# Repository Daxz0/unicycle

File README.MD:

# About

i was particulary inspired by instagram reels that showed robots demonstrating PID

i have some new members for my VEX Robotics team who are going to be learning about PID soon for their robots, so I wanted a nice way to demonstrate the concept since there are a lot of other variables when tuning a VEX robot.

### Assembly
The following includes which each component in the BOM.csv correlates to the reference on the PCB:

| Reference        | Component                  |
| ---------------- | -------------------------- |
| C1               | Aluminum Capacitor (100µF) |
| C2               | Aluminum Capacitor (330µF) |
| C3, C5           | Ceramic Capacitor (22µF)   |
| C4, C6, C8, C10  | Ceramic Capacitor (0.1µF)  |
| C7               | Ceramic Capacitor (10nF)   |
| C9               | Ceramic Capacitor (2.2nF)  |
| R1               | Resistor (330Ω)            |
| R4, R7           | Resistor (4.7kΩ)           |
| R5, R6           | Resistor (5.1kΩ)           |
| L1               | Power Inductor             |
| D1, D4           | Schottky Diode             |
| D2               | General Purpose Diode      |
| D3               | LED                        |
| D5               | Schottky Diode (Silicon)   |
| U1               | ESP32-S3-MINI-1-N8         |
| U2               | Buck Regulator             |
| U3               | LDO Regulator              |
| U4               | MPU-6050 (IMU)             |
| F1               | Fuse                       |
| SW1              | Switch                     |
| J1               | Battery Connector (XT30)   |
| J3               | USB-C                      |
| A1               | Motor Driver               |

### Resources
thanks to all these incredible resources that allowed me to put the cad together
- https://grabcad.com/library/nema-17-bracket-1
- https://grabcad.com/library/2s-7-4v-li-po-battery-1
- https://grabcad.com/library/pololu-scooter-skate-wheel-70x25mm-1
- https://a.pololu-files.com/picture/0J5557.600.jpg?7958d675b1fec8d1f6bb65c62e140bbe

note: the adapter for the wheel shaft i made myself as i could not find an existing CAD for it, linked instead is a reference sheet i used to make my own

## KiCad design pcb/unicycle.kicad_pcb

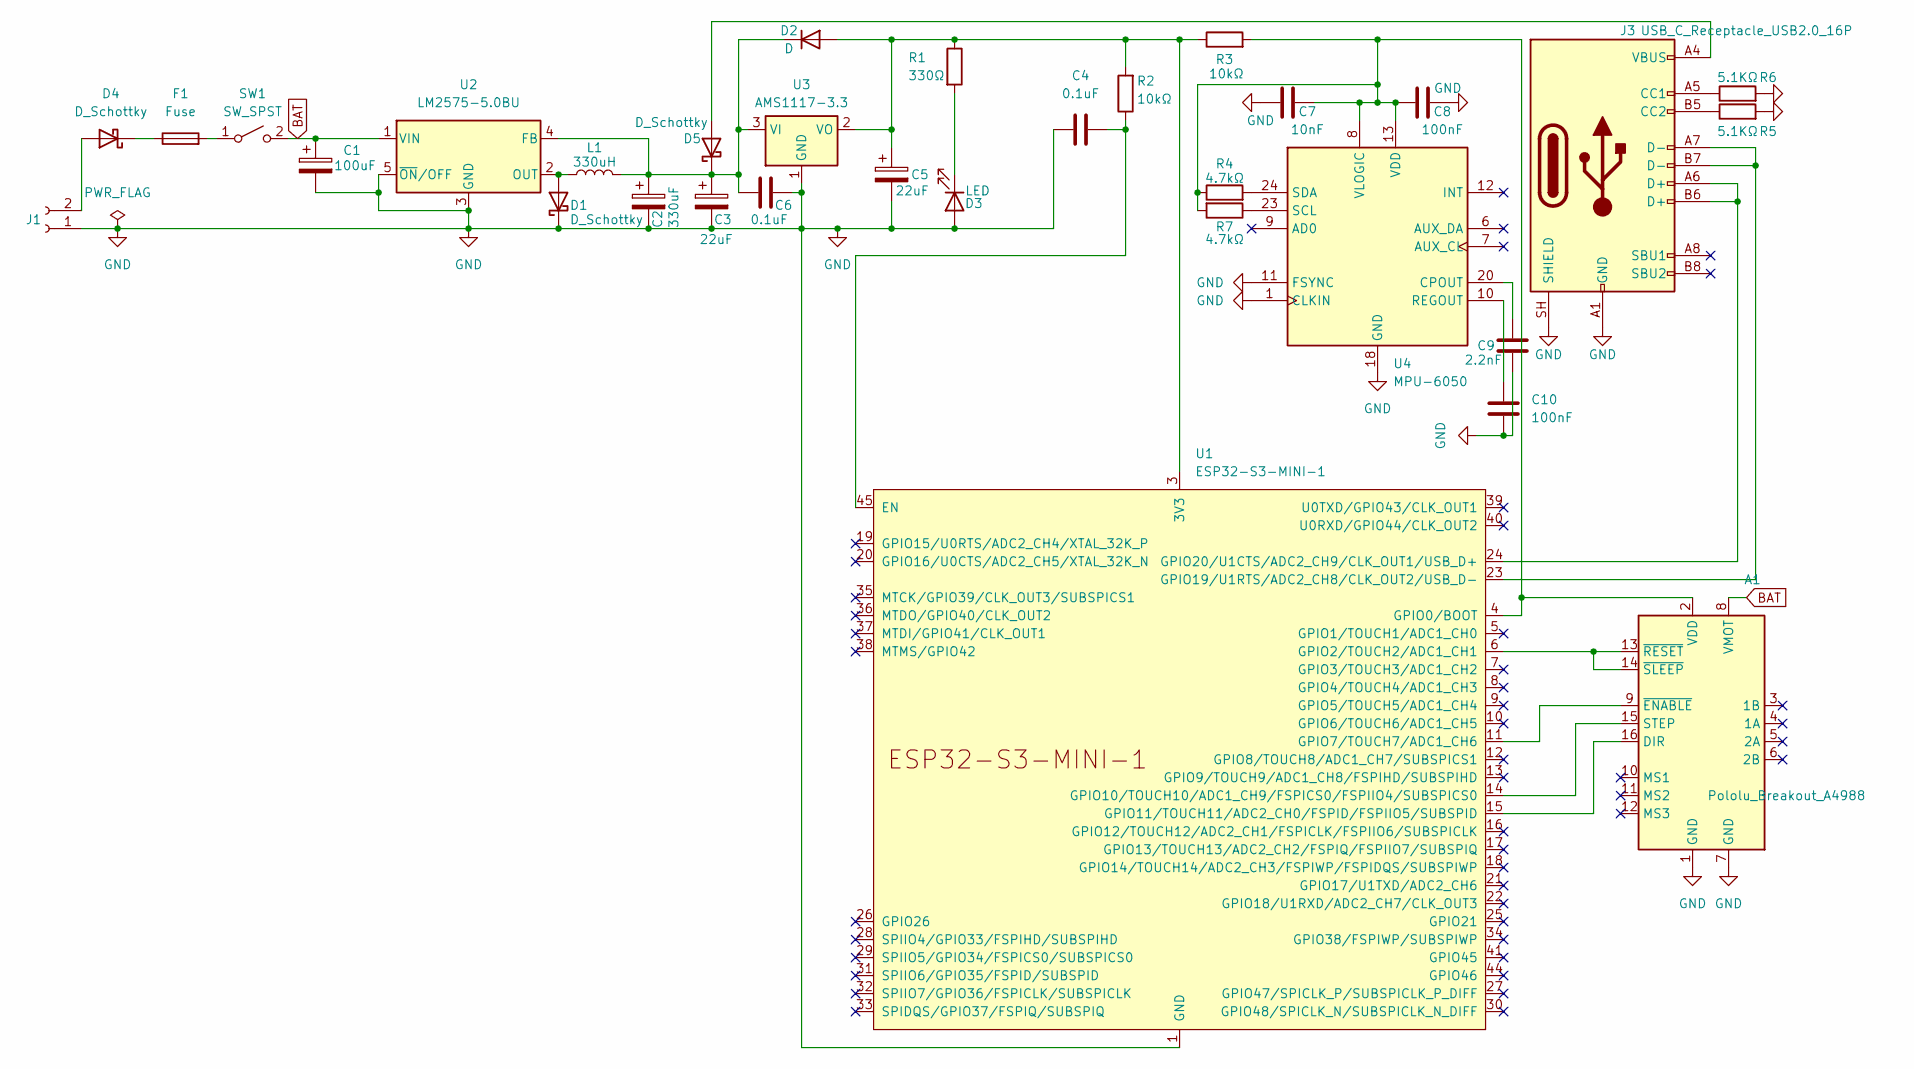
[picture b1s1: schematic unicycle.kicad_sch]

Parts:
A1: Pololu_Breakout_A4988; Pololu_Breakout-16_15.2x20.3mm
C1: 100uF; CP_Radial_D6.3mm_P2.50mm
C2: 330uF; CP_Radial_D8.0mm_P3.50mm
C3: 22uF; C_0805_2012Metric_Pad1.18x1.45mm_HandSolder
C4, C6: 0.1uF; C_0805_2012Metric_Pad1.18x1.45mm_HandSolder
C5: 22uF; D_0805_2012Metric_Pad1.15x1.40mm_HandSolder
C7: 10nF; C_0805_2012Metric_Pad1.18x1.45mm_HandSolder
C8, C10: 100nF; C_0805_2012Metric_Pad1.18x1.45mm_HandSolder
C9: 2.2nF; C_0805_2012Metric_Pad1.18x1.45mm_HandSolder
D1, D4: D_Schottky; D_DO-15_P15.24mm_Horizontal
D2: D; D_SOD-123F
D3: LED; LED_0805_2012Metric_Pad1.15x1.40mm_HandSolder
D5: D_Schottky; D_SMA
F1: Fuse; Fuse_1206_3216Metric_Pad1.42x1.75mm_HandSolder
J1: Conn_01x02_Socket; AMASS_XT30U-F_1x02_P5.0mm_Vertical
J3: USB_C_Receptacle_USB2.0_16P; USB_C_Receptacle_HCTL_HC-TYPE-C-16P-01A
L1: 330uH; L_Toroid_Vertical_L21.6mm_W11.4mm_P7.62mm_Pulse_KM-3
R1: 330Ω; R_0805_2012Metric_Pad1.20x1.40mm_HandSolder
R2, R3: 10kΩ; R_0805_2012Metric_Pad1.20x1.40mm_HandSolder
R4, R7: 4.7kΩ; R_0805_2012Metric_Pad1.20x1.40mm_HandSolder
R5, R6: 5.1KΩ; R_0805_2012Metric_Pad1.20x1.40mm_HandSolder
SW1: SW_SPST; SW_SPDT_CK_JS102011SAQN
U1: ESP32-S3-MINI-1
U2: LM2575-5.0BU; TO-263-5_TabPin3
U3: AMS1117-3.3; SOT-223-3_TabPin2
U4: MPU-6050; InvenSense_QFN-24_4x4mm_P0.5mm

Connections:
BAT: A1.8 (VMOT), C1.1, SW1.2 (B), U2.1 (VIN)
GND: A1.1 (GND), A1.7 (GND), C1.2, C2.2, C3.2, C4.1, C5.2, C6.1, C7.1, C8.2, C9.2, C10.2, D1.1 (K), D3.2 (A), J1.1, J3.A1 (GND), J3.A12 (GND), J3.B1 (GND), J3.B12 (GND), J3.SH (SHIELD), R5.2, R6.2, U1.1 (GND), U1.2 (GND), U1.42 (GND), U1.43 (GND), U1.46 (GND), U1.47 (GND), U1.48 (GND), U1.49 (GND), U1.50 (GND), U1.51 (GND), U1.52 (GND), U1.53 (GND), U1.54 (GND), U1.55 (GND), U1.56 (GND), U1.57 (GND), U1.58 (GND), U1.59 (GND), U1.60 (GND), U1.61 (GND), U1.62 (GND), U1.63 (GND), U1.64 (GND), U1.65 (GND), U2.3 (GND), U2.5 (~ON/OFF), U3.1 (GND), U4.1 (CLKIN), U4.11 (FSYNC), U4.18 (GND)
unnamed: A1.16 (DIR), U1.15 (GPIO11/TOUCH11/ADC2_CH0/FSPID/FSPIIO5/S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)
unnamed: A1.15 (STEP), U1.14 (GPIO10/TOUCH10/ADC1_CH9/FSPICS0/FSPIIO4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)
unnamed: A1.2 (VDD), C7.2, C8.1, R3.2, R4.1, R7.2, U1.4 (GPIO0/BOOT), U4.8 (VLOGIC), U4.13 (VDD)
unnamed: A1.9 (~ENABLE), U1.11 (GPIO7/TOUCH7/ADC1_CH6)
unnamed: A1.13 (~RESET), A1.14 (~SLEEP), U1.6 (GPIO2/TOUCH2/ADC1_CH1)
unnamed: D1.2 (A), L1.1, U2.2 (OUT)
unnamed: C5.1, D2.2 (A), R1.1, R2.2, R3.1, U1.3 (3V3), U3.2 (VO)
unnamed: C2.1, C3.1, C6.2, D2.1 (K), D5.1 (K), L1.2, U2.4 (FB), U3.3 (VI)
unnamed: D3.1 (K), R1.2
unnamed: D4.2 (A), J1.2
unnamed: D4.1 (K), F1.1
unnamed: D5.2 (A), J3.A4 (VBUS), J3.A9 (VBUS), J3.B4 (VBUS), J3.B9 (VBUS)
unnamed: J3.A5 (CC1), R6.1
unnamed: J3.B5 (CC2), R5.1
unnamed: F1.2, SW1.1 (A)
unnamed: C4.2, R2.1, U1.45 (EN)
unnamed: J3.A7 (D-), J3.B7 (D-), U1.23 (GPIO19/U1RTS/ADC2_CH8/CLK_OUT2/USB_D-)
unnamed: J3.A6 (D+), J3.B6 (D+), U1.24 (GPIO20/U1CTS/ADC2_CH9/CLK_OUT1/USB_D+)
unnamed: C9.1, U4.20 (CPOUT)
unnamed: C10.1, U4.10 (REGOUT)
unnamed: R7.1, U4.23 (SCL)
unnamed: R4.2, U4.24 (SDA)

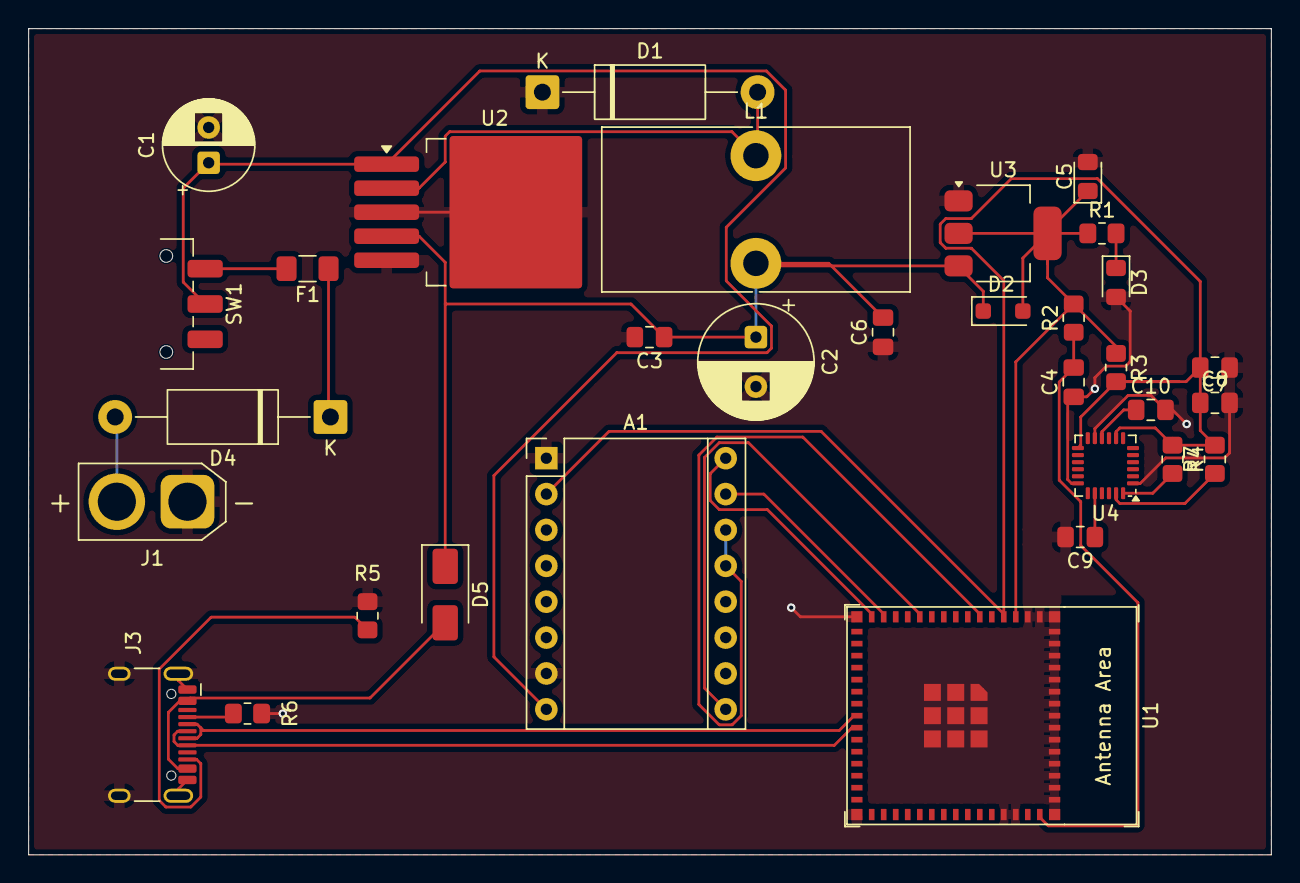
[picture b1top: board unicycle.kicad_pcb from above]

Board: 2 copper layers, 88.0 x 58.5 mm, 32 parts (0 on the bottom side), 24 nets.
